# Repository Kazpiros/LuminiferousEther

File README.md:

# Wham!

## This is
>Taking me too long to finish
---
Specs: 
**RP2350**
- Has mac instructions
- Multithreadding
- pio
- 150 MHz
---

#TODO
- Fix ADC input 
  - My theory is R7 is loading down the Guitar. need 50-100k to fix this.
- RTOS
- PASSTHRU
- CONIDITIONING
- ORDER BRAIN
- DO EFFECTS
---

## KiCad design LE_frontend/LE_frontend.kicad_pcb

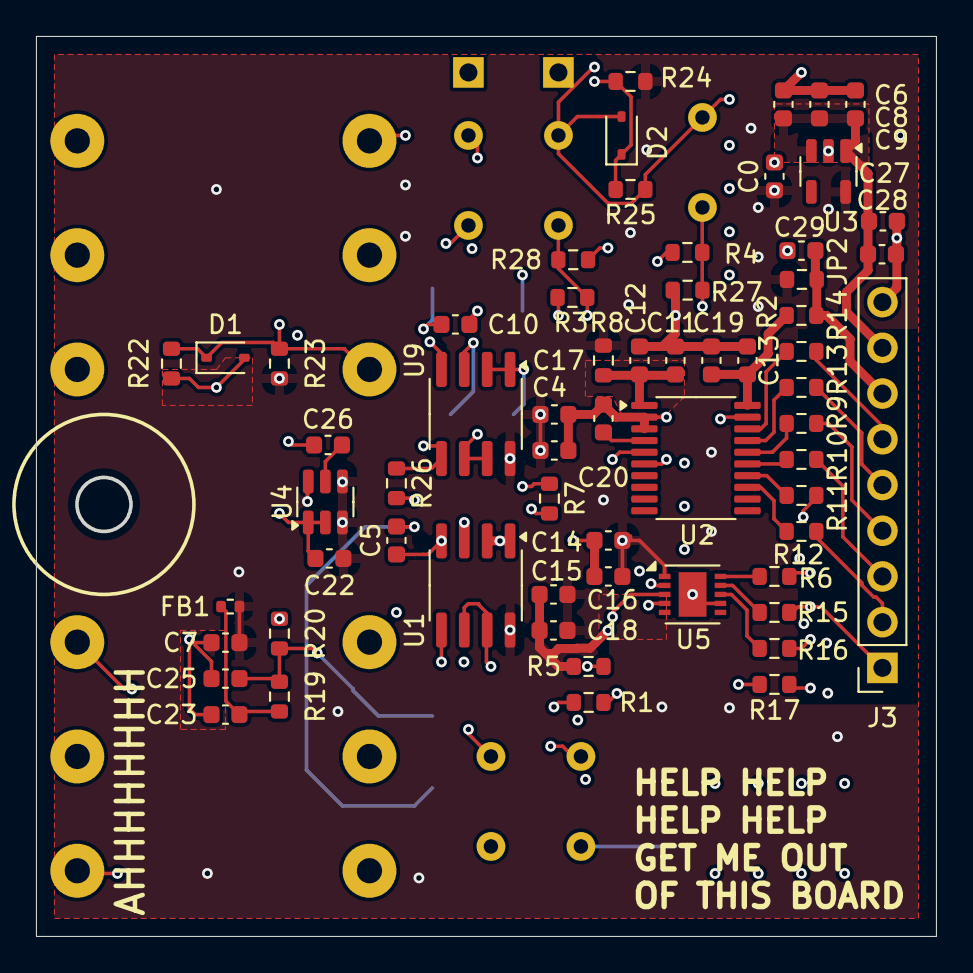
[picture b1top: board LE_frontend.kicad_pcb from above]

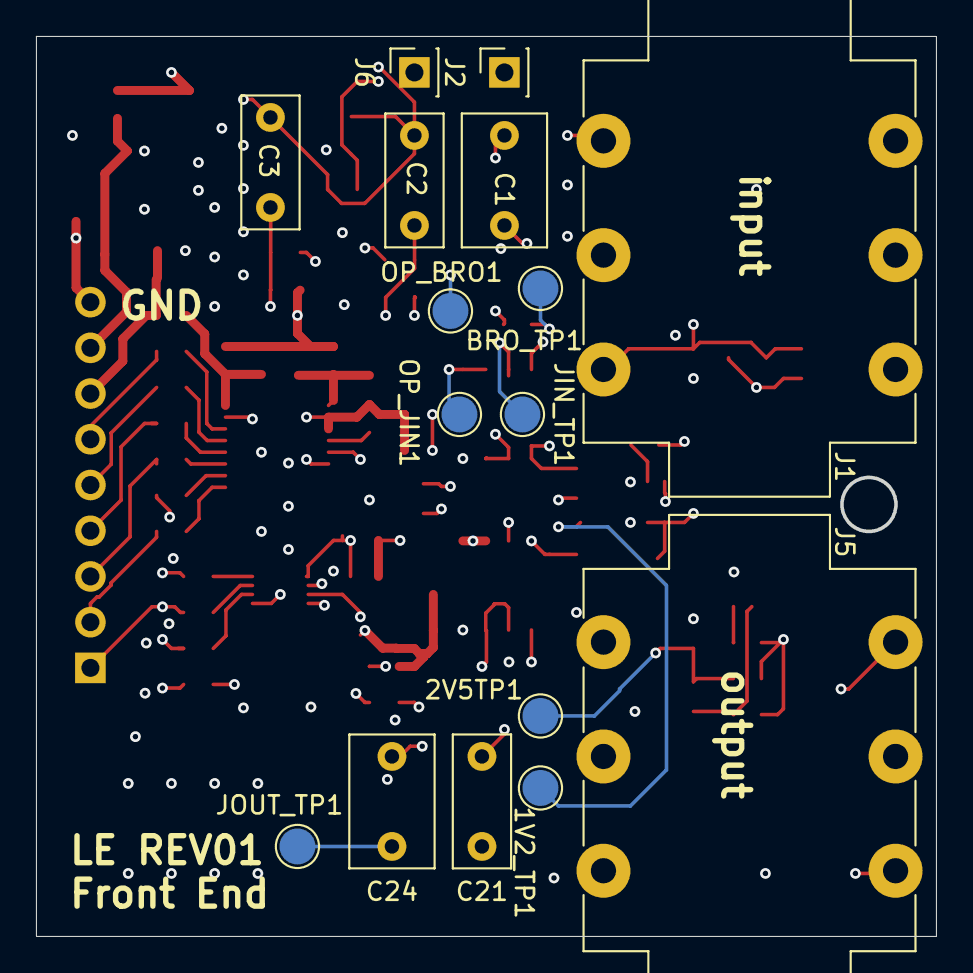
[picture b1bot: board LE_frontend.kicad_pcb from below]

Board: 6 copper layers, 49.9 x 49.9 mm, 78 parts (16 on the bottom side), 40 nets.

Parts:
1V2_TP1, 2V5TP1: TestPoint; TestPoint_Pad_D2.0mm
BRO_TP1: TestPoint; TestPoint_Pad_D2.0mm
C0, C5, C7, C10, C28, C29: 1u; C_0603_1608Metric
C1, C24: 1u; C_Rect_L7.2mm_W4.5mm_P5.00mm_FKS2_FKP2_MKS2_MKP2
C2, C3: 47n; C_Rect_L7.2mm_W3.0mm_P5.00mm_FKS2_FKP2_MKS2_MKP2
C4, C8, C11, C12, C13, C15, C16, C17, C18, C19, C20, C22, C23, C25, C26: 0.1u; C_0603_1608Metric
C6, C9, C14, C27: 10u; C_0603_1608Metric
C21: 0.1u; C_Rect_L7.2mm_W3.0mm_P5.00mm_FKS2_FKP2_MKS2_MKP2
D1, D2: TSD05CDYFR; D_SOD-323
FB1: FerriteBead_Small; R_0402_1005Metric
J1, J5: Barrel_Jack; Jack_6.35mm_Neutrik_NMJ6HFD2_Horizontal
J2, J6: Conn_01x01; PinSocket_1x01_P2.54mm_Vertical
J3: Conn_01x06; PinSocket_1x09_P2.54mm_Vertical
JIN_TP1: TestPoint; TestPoint_Pad_D2.0mm
JOUT_TP1: TestPoint; TestPoint_Pad_D2.0mm
JP2: Jumper_2_Bridged; R_0603_1608Metric
OP_BRO1: TestPoint; TestPoint_Pad_D2.0mm
OP_JIN1: TestPoint; TestPoint_Pad_D2.0mm
R1, R3, R4: 100; R_0603_1608Metric
R2, R8, R17: 33; R_0603_1608Metric
R5, R22, R23, R24, R25: 1Meg; R_0603_1608Metric
R6, R9, R10, R11, R12, R13, R14, R15, R16: 10; R_0603_1608Metric
R7, R26: 1k; R_0603_1608Metric
R19: 2.4k; R_0603_1608Metric
R20: 7.5k; R_0603_1608Metric
R27, R28: 10k; R_0603_1608Metric
U1, U9: LME49721; SOIC-8_3.9x4.9mm_P1.27mm
U2: MCP3461RT-E/ST; TSSOP-20_4.4x6.5mm_P0.65mm
U3: NCP163ASN330T1G; SOT-23-5
U4: REF35120QDBVR; SOT-23-6
U5: MCP48CVD21T-E/MF; DFN-10-1EP_3x3mm_P0.5mm_EP1.55x2.48mm

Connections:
+3V3_Analog: C0.1, C4.2, C7.2, C14.2, C15.2, C16.2, C17.2, C18.2, C22.2, FB1.1, JP2.1 (A), R8.1, R23.1, R24.1, U1.8 (V+), U3.5 (VOUT), U4.3 (EN), U4.4 (VIN), U5.1 (VDD), U9.8 (V+)
+3V3_DIG: C29.1, J3.7, JP2.2 (B), R2.2
/1V2: R7.2, R26.2, U1.1, U1.2 (-)
/2V5: 2V5TP1.1, C25.2, R19.2, R20.1, U5.3 (VREF)
/2V5_INPUT_FILTER: C23.2, FB1.2, R19.1
/ADC_PWR_AVDD: C11.2, C12.2, R8.2, U2.1 (AVDD)
/ADC_PWR_DVDD: C13.2, C19.2, R2.1, U2.20 (DVDD)
/IN+: C2.2, R3.2, R28.2, U2.5 (CH0)
/IN-: C3.2, R4.2, R27.2, U2.6 (CH1)
/MCLK: J3.6, R14.1
/Neg_input_Header: C10.1, D2.1 (A1), J2.1, R24.2, R25.1
/OUTPUT_SIG: C24.2, J5.T, JOUT_TP1.1, R5.1
/POS_INPUT_SIG: C1.1, D1.1 (A1), J1.T, R22.1, R23.2
/SCK: J3.1, R11.1, R15.1
/SDI: J3.3, R6.1, R10.1
/SDO: J3.4, R9.1, R16.1
/U1_INPUT_SIG: C21.2, R1.2, U1.5 (+)
/U1_OUTPUT_SIG: C24.1, U1.6 (-), U1.7
/U1_REFERENCE_NON-INVERTING: 1V2_TP1.1, C5.2, U1.3 (+), U4.6 (VREF)
/U9_input_neg: BRO_TP1.1, C10.2, R26.1, U9.5 (+)
/U9_output_neg: OP_BRO1.1, R4.1, U9.6 (-), U9.7
/U9_output_pos: OP_JIN1.1, R3.1, U9.1, U9.2 (-)
/VOUT: R1.1, U5.4 (VOUT)
//CS: J3.2, R12.1, R17.1
//IRQ: J3.5, R13.1
GND: C0.2, C2.1, C3.1, C4.1, C5.1, C6.2, C7.1, C8.2, C9.2, C11.1, C12.1, C13.1, C14.1, C15.1, C16.1, C17.1, C18.1, C19.1, C20.1, C21.1, C22.1, C23.1, C25.1, C26.1, C27.2, C28.2, C29.2, D1.2 (A2), D2.2 (A2), J1.S, J3.9, J5.S, J6.1, R5.2, R20.2, R22.2, R25.2, R27.1, R28.1, U1.4 (V-), U2.2 (AGND), U2.3 (REFIN-), U2.19 (DGND), U3.2 (GND), U4.1 (GND), U4.2 (GND), U5.7 (VSS), U5.11 (VSS), U9.4 (V-)
unnamed: R12.2, U2.13 (*CS)
unnamed: R13.2, U2.17 (*IRQ/MDAT)
unnamed: R14.2, U2.18 (MCLK)
unnamed: C20.2, U2.4 (REFIN+/OUT)
unnamed: R11.2, U2.14 (SCK)
unnamed: R10.2, U2.15 (SDI)
unnamed: R9.2, U2.16 (SDO)
unnamed: C26.2, U4.5 (NR)
unnamed: R17.2, U5.2 (*CS)
unnamed: R15.2, U5.9 (SCK)
unnamed: R6.2, U5.10 (SDI)
unnamed: R16.2, U5.8 (SDO)
unnamed: C1.2, JIN_TP1.1, R7.1, U9.3 (+)
Vin: C6.1, C8.1, C9.1, C27.1, C28.1, J3.8, U3.1 (VIN), U3.3 (EN)

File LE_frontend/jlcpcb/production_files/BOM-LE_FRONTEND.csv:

Comment,Designator,Footprint,LCSC,Quantity
0.1u,"C11,C12,C13,C15,C16,C17,C18,C19,C20,C22,C23,C25,C26,C4,C8",C_0603_1608Metric,C14663,15
1u,"C0,C10,C28,C29,C5,C7",C_0603_1608Metric,C15849,6
Jumper_2_Bridged,JP2,R_0603_1608Metric,C21189,1
100,"R1,R26,R3,R4,R7",R_0603_1608Metric,C22775,5
10,"R10,R11,R12,R13,R14,R15,R16,R6,R9",R_0603_1608Metric,C22859,9
1Meg,"R22,R24,R25,R5",R_0603_1608Metric,C22935,4
2.4k,R19,R_0603_1608Metric,C22940,1
33,"R17,R2,R8",R_0603_1608Metric,C23140,3
7.5k,R20,R_0603_1608Metric,C23234,1
10k,R28,R_0603_1608Metric,C25197,1
10u,"C14,C27,C6,C9",C_0603_1608Metric,C96446,4
FerriteBead_Small,FB1,R_0402_1005Metric,,1
TSD05CDYFR,D1,D_SOD-323,,1
TSD05CDYFR,D2,D_SOD-323,,1
LME49721,U9,SOIC-8_3.9x4.9mm_P1.27mm,,1
MCP3461RT-E/ST,U2,TSSOP-20_4.4x6.5mm_P0.65mm,,1
MCP48CVD21T-E/MF,U5,DFN-10-1EP_3x3mm_P0.5mm_EP1.55x2.48mm,,1
Conn_01x06,J3,PinSocket_1x09_P2.54mm_Vertical,,1
NCP163ASN330T1G,U3,SOT-23-5,,1
REF35120QDBVR,U4,SOT-23-6,,1
LME49721,U1,SOIC-8_3.9x4.9mm_P1.27mm,,1
47n,C2,C_Rect_L7.2mm_W3.0mm_P5.00mm_FKS2_FKP2_MKS2_MKP2,,1
Barrel_Jack,J5,Jack_6.35mm_Neutrik_NMJ6HFD2_Horizontal,,1
TestPoint,JIN_TP1,TestPoint_Pad_D2.0mm,,1
0.1u,C21,C_Rect_L7.2mm_W3.0mm_P5.00mm_FKS2_FKP2_MKS2_MKP2,,1
1u,C24,C_Rect_L7.2mm_W4.5mm_P5.00mm_FKS2_FKP2_MKS2_MKP2,,1
Barrel_Jack,J1,Jack_6.35mm_Neutrik_NMJ6HFD2_Horizontal,,1
TestPoint,1V2_TP1,TestPoint_Pad_D2.0mm,,1
TestPoint,OP_BRO1,TestPoint_Pad_D2.0mm,,1
TestPoint,JOUT_TP1,TestPoint_Pad_D2.0mm,,1
TestPoint,2V5TP1,TestPoint_Pad_D2.0mm,,1
1u,C1,C_Rect_L7.2mm_W4.5mm_P5.00mm_FKS2_FKP2_MKS2_MKP2,,1
TestPoint,BRO_TP1,TestPoint_Pad_D2.0mm,,1
Conn_01x01,J2,PinSocket_1x01_P2.54mm_Vertical,,1
47n,C3,C_Rect_L7.2mm_W3.0mm_P5.00mm_FKS2_FKP2_MKS2_MKP2,,1
Conn_01x01,J6,PinSocket_1x01_P2.54mm_Vertical,,1
TestPoint,OP_JIN1,TestPoint_Pad_D2.0mm,,1

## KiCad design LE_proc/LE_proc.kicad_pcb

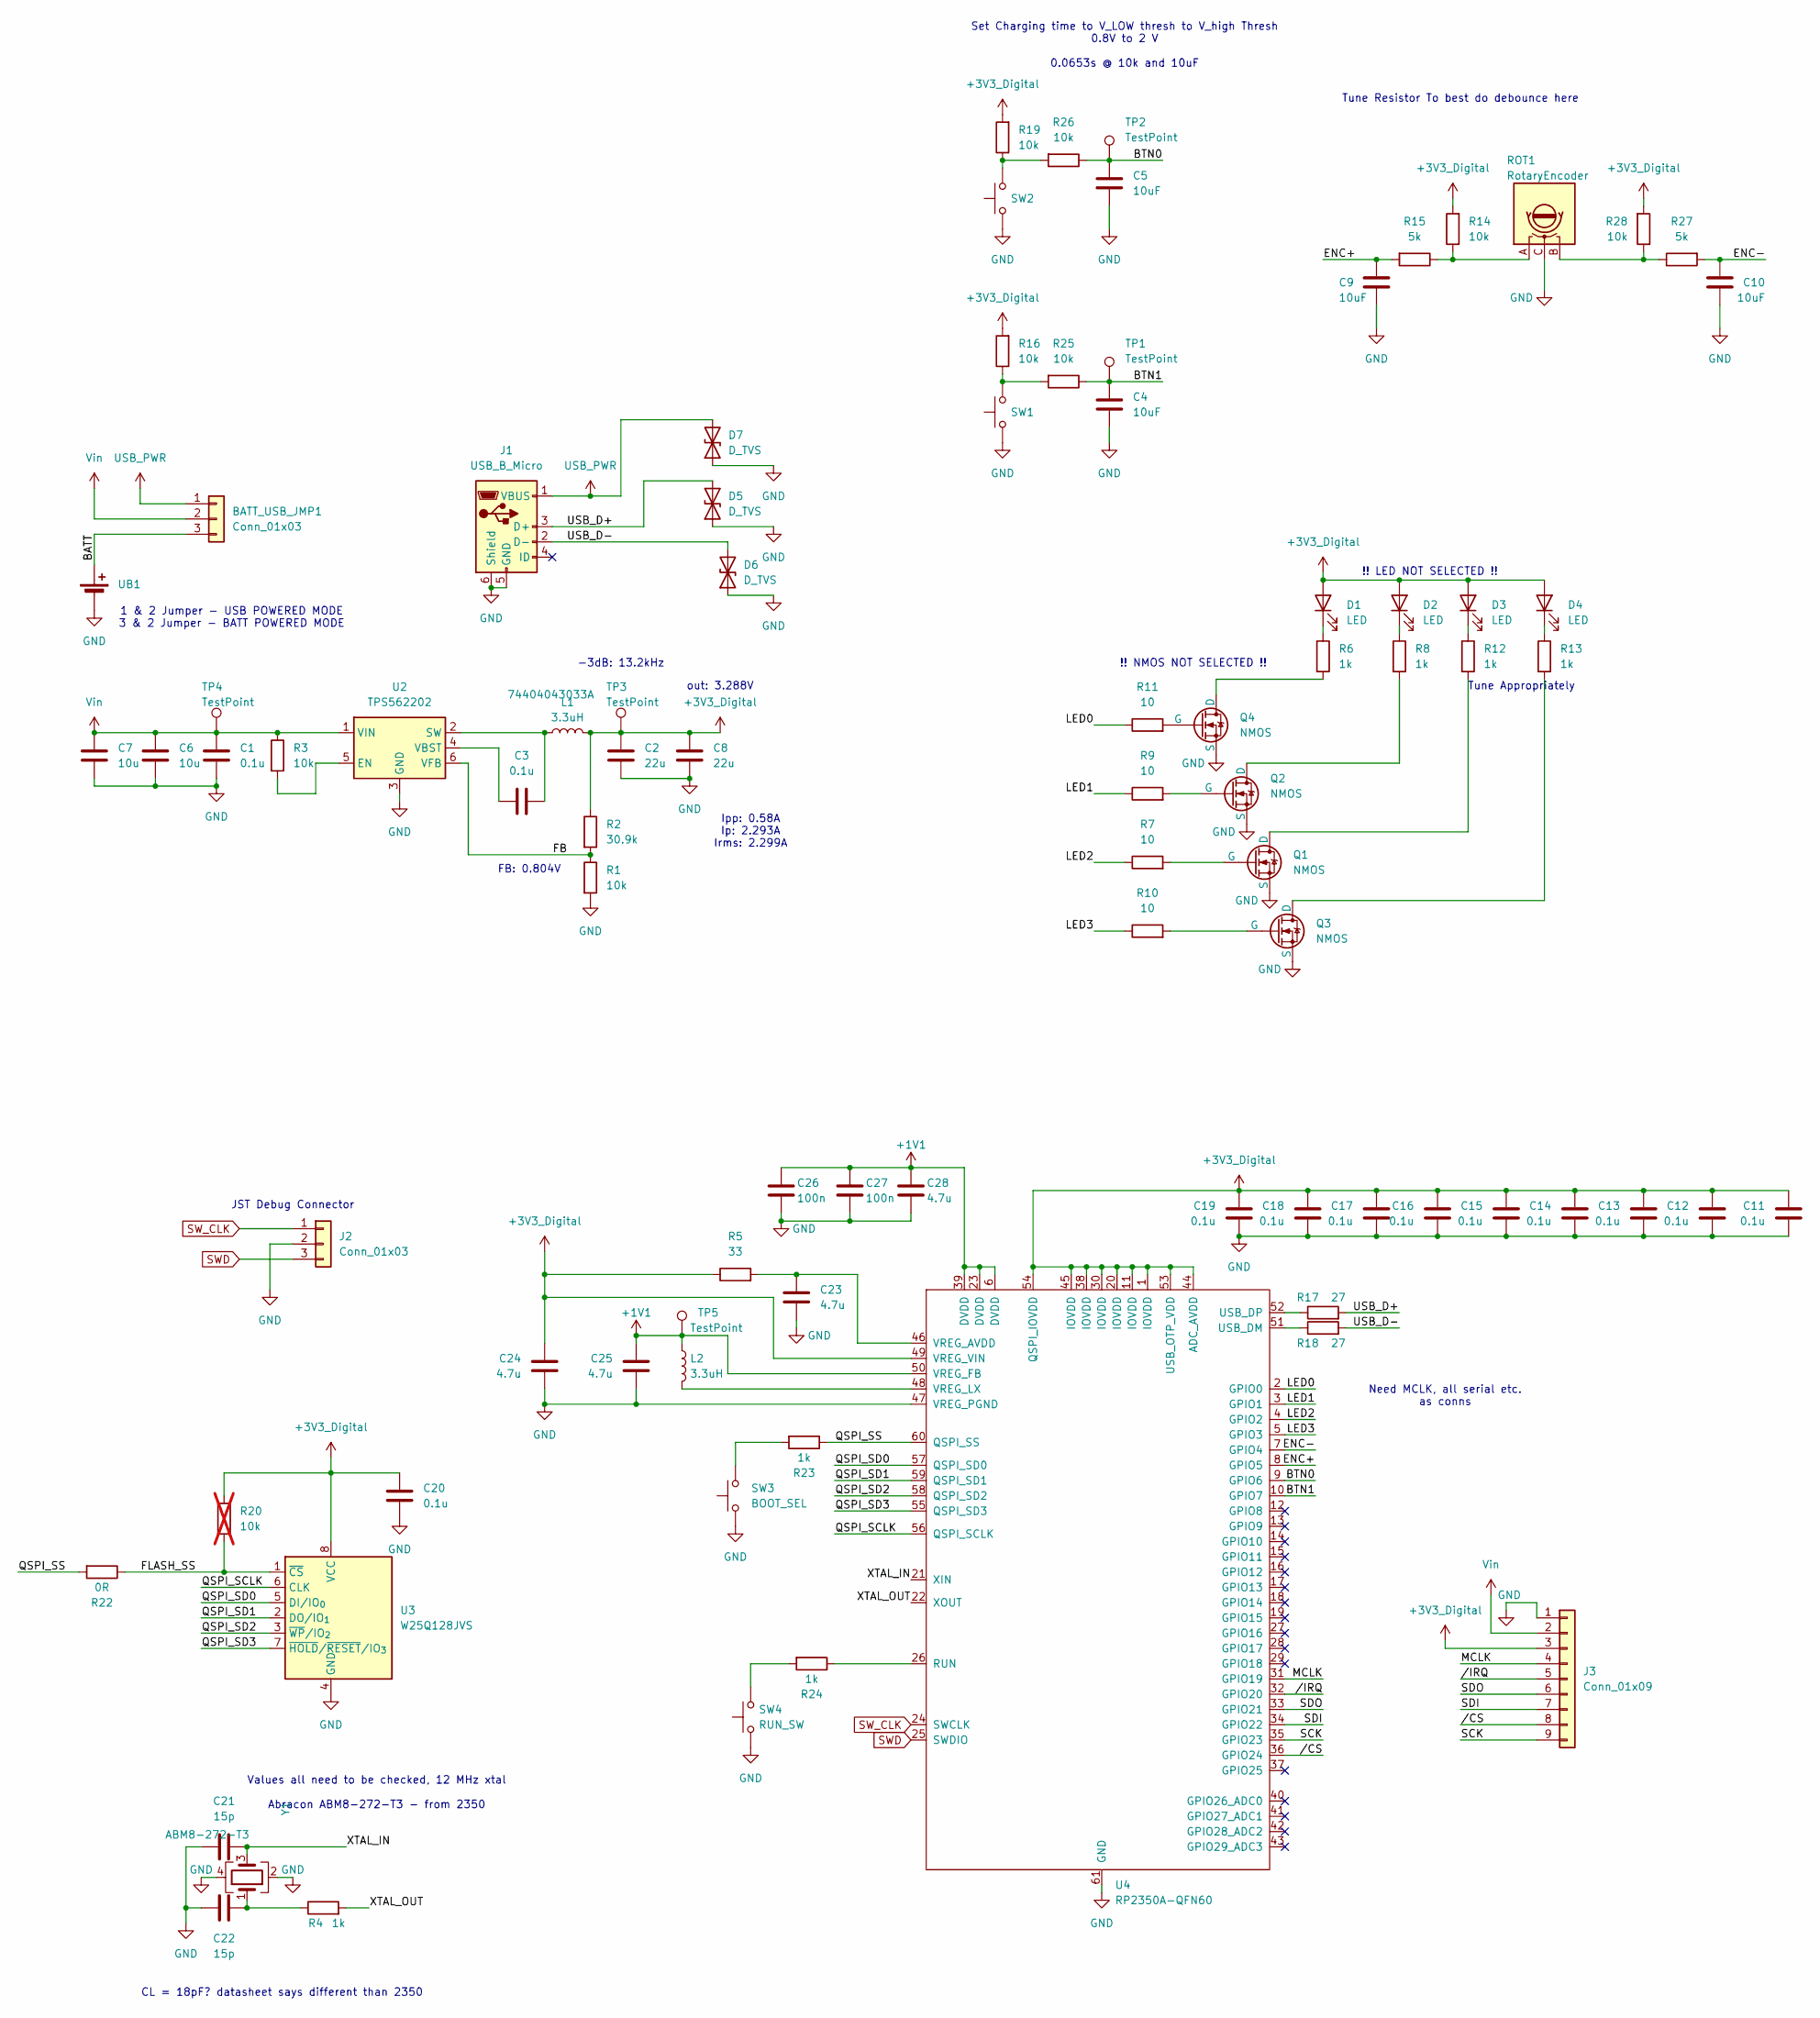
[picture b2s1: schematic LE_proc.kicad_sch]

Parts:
BATT_USB_JMP1: Conn_01x03; PinSocket_1x03_P2.54mm_Vertical
C1, C3, C11, C12, C13, C14, C15, C16, C17, C18, C19, C20: 0.1u; C_0402_1005Metric
C2, C8: 22u; C_0603_1608Metric
C4, C5, C9, C10: 10uF; C_0603_1608Metric
C6, C7: 10u; C_0402_1005Metric
C21, C22: 15p; C_0402_1005Metric
C23, C24, C25, C28: 4.7u; C_0402_1005Metric
C26, C27: 100n; C_0402_1005Metric
D1, D2, D3, D4: LED; D_0603_1608Metric
D5, D6, D7: D_TVS; D_SOD-323
J1: USB_B_Micro; USB_Micro-AB_Molex_47590-0001
J2: Conn_01x03; PinSocket_1x03_P2.54mm_Vertical
J3: Conn_01x09; PinSocket_1x09_P2.54mm_Vertical
L1, L2: 3.3uH; WE-LQS_4025
Q1, Q2, Q3, Q4: NMOS; SOT-23-3
R1, R3, R14, R16, R19, R25, R26, R28: 10k; R_0402_1005Metric
R2: 30.9k; R_0402_1005Metric
R4, R6, R8, R12, R13, R23, R24: 1k; R_0402_1005Metric
R5: 33; R_0402_1005Metric
R7, R9, R10, R11: 10; R_0402_1005Metric
R15, R27: 5k; R_0402_1005Metric
R17, R18: 27; R_0402_1005Metric
R20: 10k; R_0402_1005Metric; not fitted
R22: 0R; R_0402_1005Metric
ROT1: RotaryEncoder; RotaryEncoder_Bourns_Vertical_PEC12R-3x17F-Nxxxx
SW1, SW2: SW_Push; SW_PUSH_6mm_H5mm
SW3: BOOT_SEL; SW_PUSH_6mm_H5mm
SW4: RUN_SW; SW_PUSH_6mm_H5mm
TP1, TP2, TP3, TP4, TP5: TestPoint; TestPoint_Pad_D2.0mm
U2: TPS562202; SOT-563
U3: W25Q128JVS; SOIC-8_5.3x5.3mm_P1.27mm
U4: RP2350A-QFN60; QFN-60-1EP_7x7mm_P0.4mm_EP3.4x3.4mm
UB1: Battery; TerminalBlock_Phoenix_MKDS-1,5-2_1x02_P5.00mm_Horizontal
Y1: ABM8-272-T3; Crystal_SMD_Abracon_ABM3-2Pin_5.0x3.2mm

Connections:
+1V1: C25.1, C26.1, C27.1, C28.1, L2.1, TP5.1, U4.6 (DVDD), U4.23 (DVDD), U4.39 (DVDD), U4.50 (VREG_FB)
+3V3_Digital: C2.1, C8.1, C11.1, C12.1, C13.1, C14.1, C15.1, C16.1, C17.1, C18.1, C19.1, C20.1, C24.1, D1.2 (A), D2.2 (A), D3.2 (A), D4.2 (A), J3.3, L1.2, R2.1, R5.1, R14.2, R16.2, R19.2, R20.2, R28.2, TP3.1, U3.8 (VCC), U4.1 (IOVDD), U4.11 (IOVDD), U4.20 (IOVDD), U4.30 (IOVDD), U4.38 (IOVDD), U4.44 (ADC_AVDD), U4.45 (IOVDD), U4.49 (VREG_VIN), U4.53 (USB_OTP_VDD), U4.54 (QSPI_IOVDD)
/BATT: BATT_USB_JMP1.3, UB1.1 (+)
/BTN0: C5.2, R26.1, TP2.1, U4.9 (GPIO6)
/BTN1: C4.2, R25.1, TP1.1, U4.10 (GPIO7)
/ENC+: C9.2, R15.2, U4.8 (GPIO5)
/ENC-: C10.2, R27.2, U4.7 (GPIO4)
/FB: R1.1, R2.2, U2.6 (VFB)
/FLASH_SS: R20.1, R22.1, U3.1 (~CS)
/LED0: R11.1, U4.2 (GPIO0)
/LED1: R9.1, U4.3 (GPIO1)
/LED2: R7.1, U4.4 (GPIO2)
/LED3: R10.1, U4.5 (GPIO3)
/MCLK: J3.4, U4.31 (GPIO19)
/QSPI_SCLK: U3.6 (CLK), U4.56 (QSPI_SCLK)
/QSPI_SD0: U3.5 (DI/IO_{0}), U4.57 (QSPI_SD0)
/QSPI_SD1: U3.2 (DO/IO_{1}), U4.59 (QSPI_SD1)
/QSPI_SD2: U3.3 (~WP/IO_{2}), U4.58 (QSPI_SD2)
/QSPI_SD3: U3.7 (~HOLD/~RESET/IO_{3}), U4.55 (QSPI_SD3)
/QSPI_SS: R22.2, R23.1, U4.60 (QSPI_SS)
/SCK: J3.9, U4.35 (GPIO23)
/SDI: J3.7, U4.34 (GPIO22)
/SDO: J3.6, U4.33 (GPIO21)
/USB_D+: D5.2 (A2), J1.3 (D+), R17.2
/USB_D-: D6.2 (A2), J1.2 (D-), R18.2
/XTAL_IN: C21.2, U4.21 (XIN), Y1.3
/XTAL_OUT: R4.2, U4.22 (XOUT)
//CS: J3.8, U4.36 (GPIO24)
//IRQ: J3.5, U4.32 (GPIO20)
GND: C1.2, C2.2, C4.1, C5.1, C6.2, C7.2, C8.2, C9.1, C10.1, C11.2, C12.2, C13.2, C14.2, C15.2, C16.2, C17.2, C18.2, C19.2, C20.2, C21.1, C22.1, C23.2, C24.2, C25.2, C26.2, C27.2, C28.2, D5.1 (A1), D6.1 (A1), D7.1 (A1), J1.5 (GND), J1.6 (Shield), J2.2, J3.1, Q1.3 (S), Q2.3 (S), Q3.3 (S), Q4.3 (S), R1.2, ROT1.C, SW1.1, SW2.1, SW3.1, SW4.1, U2.3 (GND), U3.4 (GND), U4.47 (VREG_PGND), U4.61 (GND), UB1.2 (-), Y1.2, Y1.4; also elsewhere on the board
unnamed: C22.2, R4.1, Y1.1
unnamed: D1.1 (K), R6.1
unnamed: D2.1 (K), R8.1
unnamed: D3.1 (K), R12.1
unnamed: D4.1 (K), R13.1
unnamed: Q1.1 (D), R12.2
unnamed: Q1.2 (G), R7.2
unnamed: Q2.1 (D), R8.2
unnamed: Q2.2 (G), R9.2
unnamed: Q3.1 (D), R13.2
unnamed: Q3.2 (G), R10.2
unnamed: Q4.1 (D), R6.2
unnamed: Q4.2 (G), R11.2
unnamed 43: R14.1, R15.1, ROT1.A; also elsewhere on the board
unnamed: R16.1, R25.2, SW1.2
unnamed: R19.1, R26.2, SW2.2
unnamed: R23.2, SW3.2
unnamed: R24.2, SW4.2
unnamed 48: R27.1, R28.1, ROT1.B; also elsewhere on the board
unnamed: R3.2, U2.5 (EN)
unnamed: C3.2, L1.1, U2.2 (SW)
unnamed: C3.1, U2.4 (VBST)
unnamed: R24.1, U4.26 (RUN)
unnamed: R18.1, U4.51 (USB_DM)
unnamed: R17.1, U4.52 (USB_DP)
unnamed: C23.1, R5.2, U4.46 (VREG_AVDD)
unnamed: L2.2, U4.48 (VREG_LX)
SWD: J2.3, U4.25 (SWDIO)
SW_CLK: J2.1, U4.24 (SWCLK)
USB_PWR: BATT_USB_JMP1.1, D7.2 (A2), J1.1 (VBUS)
Vin: BATT_USB_JMP1.2, C1.1, C6.1, C7.1, J3.2, R3.1, TP4.1, U2.1 (VIN)

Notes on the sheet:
!! NMOS NOT SELECTED !!
-3dB: 13.2kHz
Tune Appropriately
out: 3.288V
Set Charging time to V_LOW thresh to V_high Thresh 0.8V to 2 V 0.0653s @ 10k and 10uF
CL = 18pF? datasheet says different than 2350
Values all need to be checked, 12 MHz xtal Abracon ABM8-272-T3 - from 2350
FB: 0.804V
Ipp: 0.58A Ip: 2.293A Irms: 2.299A
1 & 2 Jumper - USB POWERED MODE 3 & 2 Jumper - BATT POWERED MODE
Tune Resistor To best do debounce here
JST Debug Connector
Need MCLK, all serial etc. as conns
!! LED NOT SELECTED !!

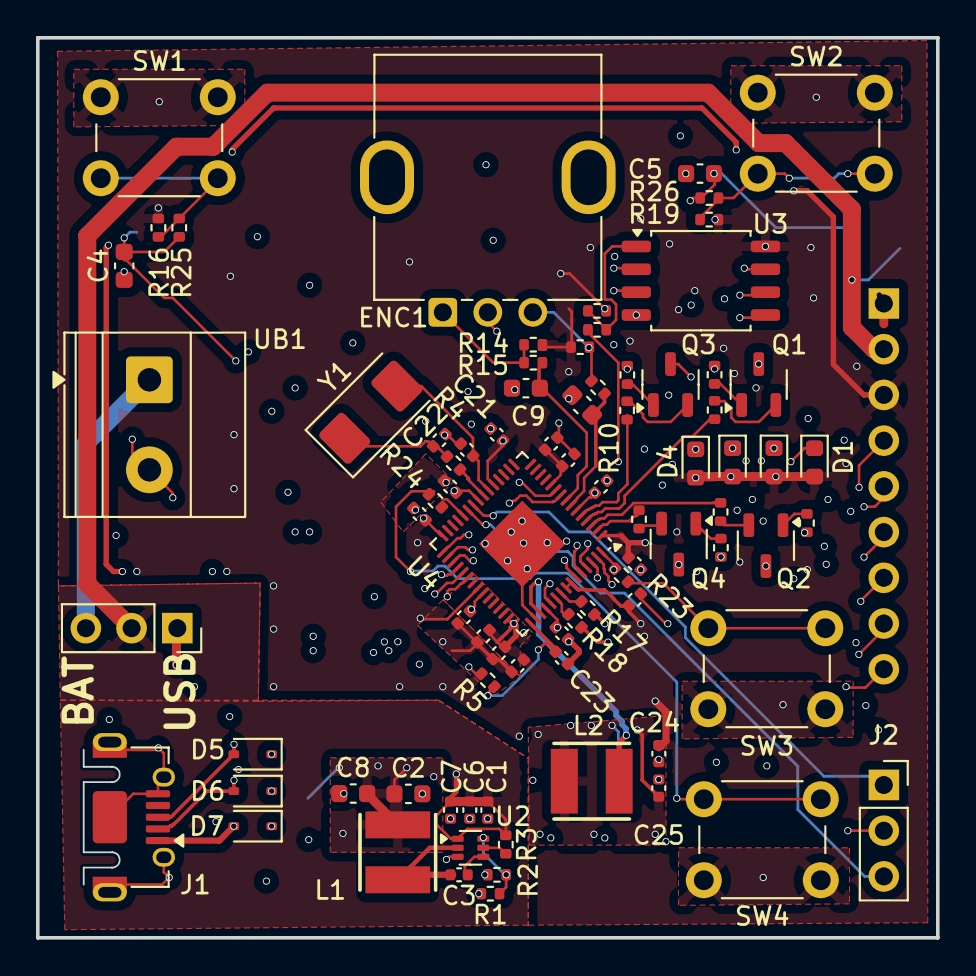
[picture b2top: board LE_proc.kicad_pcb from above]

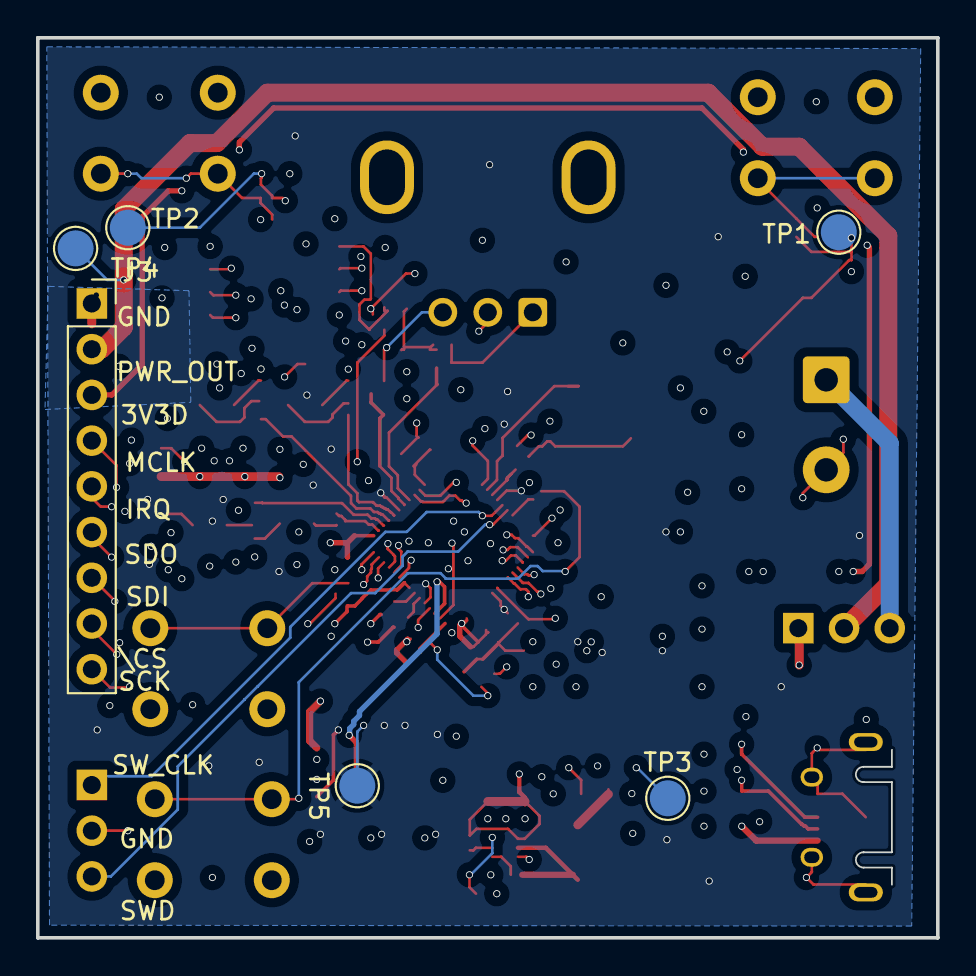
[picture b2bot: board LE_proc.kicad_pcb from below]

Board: 6 copper layers, 50.0 x 50.0 mm, 87 parts (6 on the bottom side), 61 nets.

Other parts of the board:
ENC1: RotaryEncoder; RotaryEncoder_Bourns_Vertical_PEC12R-3x17F-Nxxxx

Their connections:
GND: ENC1.C; also elsewhere on the board
unnamed 43: ENC1.A; also elsewhere on the board
unnamed 48: ENC1.B; also elsewhere on the board

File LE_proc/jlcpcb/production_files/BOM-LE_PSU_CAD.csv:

Comment,Designator,Footprint,LCSC,Quantity
1k,"R12,R13,R23,R24,R4,R6,R8",R_0402_1005Metric,C11702,7
0.1u,"C1,C11,C12,C13,C14,C15,C16,C17,C18,C19,C20,C26,C27,C3",C_0402_1005Metric,C1525,14
15p,"C21,C22",C_0402_1005Metric,C1548,2
10u,"C6,C7",C_0402_1005Metric,C15525,2
ABM8-272-T3,Y1,Crystal_SMD_Abracon_ABM3-2Pin_5.0x3.2mm,C20625731,1
LED,"D1,D2,D3,D4",D_0603_1608Metric,C2286,4
4.7u,"C23,C24,C25,C28",C_0402_1005Metric,C23733,4
27,"R17,R18",R_0402_1005Metric,C25092,2
10k,"R1,R14,R16,R19,R25,R26,R28,R3",R_0402_1005Metric,C25744,8
10,"R10,R11,R15,R27,R7,R9",R_0402_1005Metric,C25905,6
30.9k,"R2,R5",R_0402_1005Metric,C270615,2
RP2350A-QFN60,U4,QFN-60-1EP_7x7mm_P0.4mm_EP3.4x3.4mm,C42411118,1
22u,"C2,C8",C_0603_1608Metric,C59461,2
NMOS,"Q1,Q2,Q3,Q4",SOT-23-3,C8545,4
10uF,"C10,C4,C5,C9",C_0603_1608Metric,C96446,4
BOOT_SEL,SW3,SW_PUSH_6mm_H5mm,,1
W25Q128JVS,U3,SOIC-8_5.3x5.3mm_P1.27mm,,1
D_TVS,D6,D_SOD-323,,1
SW_Push,SW1,SW_PUSH_6mm_H5mm,,1
3.3uH,L1,WE-LQS_4025,,1
Battery,UB1,"TerminalBlock_Phoenix_MKDS-1,5-2_1x02_P5.00mm_Horizontal",,1
USB_B_Micro,J1,USB_Micro-AB_Molex_47590-0001,,1
RUN_SW,SW4,SW_PUSH_6mm_H5mm,,1
SW_Push,SW2,SW_PUSH_6mm_H5mm,,1
0R,R22,R_0402_1005Metric,,1
D_TVS,D7,D_SOD-323,,1
TPS562202,U2,SOT-563,,1
Conn_01x03,J2,PinSocket_1x03_P2.54mm_Vertical,,1
D_TVS,D5,D_SOD-323,,1
3.3uH,L2,WE-LQS_4025,,1
TestPoint,TP1,TestPoint_Pad_D2.0mm,,1
TestPoint,TP2,TestPoint_Pad_D2.0mm,,1
Conn_01x09,J3,PinSocket_1x09_P2.54mm_Vertical,,1
TestPoint,TP3,TestPoint_Pad_D2.0mm,,1
TestPoint,TP4,TestPoint_Pad_D2.0mm,,1
TestPoint,TP5,TestPoint_Pad_D2.0mm,,1
RotaryEncoder,ENC1,RotaryEncoder_Bourns_Vertical_PEC12R-3x17F-Nxxxx,,1
Conn_01x03,BATT_USB_JMP1,PinSocket_1x03_P2.54mm_Vertical,,1

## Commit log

2025-10-11 Squashed history
2025-10-11 Clean repo and apply proper .gitignore
2025-10-21 it works! mostly. will re-write library
2025-10-22 Added some debugging stuff
    and improved my cbuf
2025-10-23 got serial almost working, ADC READS like a charm.
2025-10-30 checkin
2025-10-31 added new pio.
2025-11-07 idk what i changed, but its so much im scared to do anything else
2025-11-07 added CAD files
2025-11-07 added some tiddly bits
2025-11-09 trying to fenagle this dac
2025-11-10 This works, irq, dma, and pio
2025-11-11 added pio. turns out dma was not needed.
